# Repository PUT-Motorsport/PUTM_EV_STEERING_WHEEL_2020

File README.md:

# PUTM_EV_STEERING_WHEEL_2022

An overview of how I see this thing working:

* ~~Data gathered from IMU will be calculated into degrees and stored in buffers. These will be send out when the buffer is filled up.~~ 
* Interrupt will be triggered if a button is pressed. Then it will determine which button was pressed and send corresponding data. If, within specified, short time, there will occur another interrupt, then the programm will treat it as different action (two buttons pressed simultaneously). There will be 10 combinations: 4 single- and 6 simultaneous-presses.
* The scroll-like switches will trigger an interrupt if its position changes.

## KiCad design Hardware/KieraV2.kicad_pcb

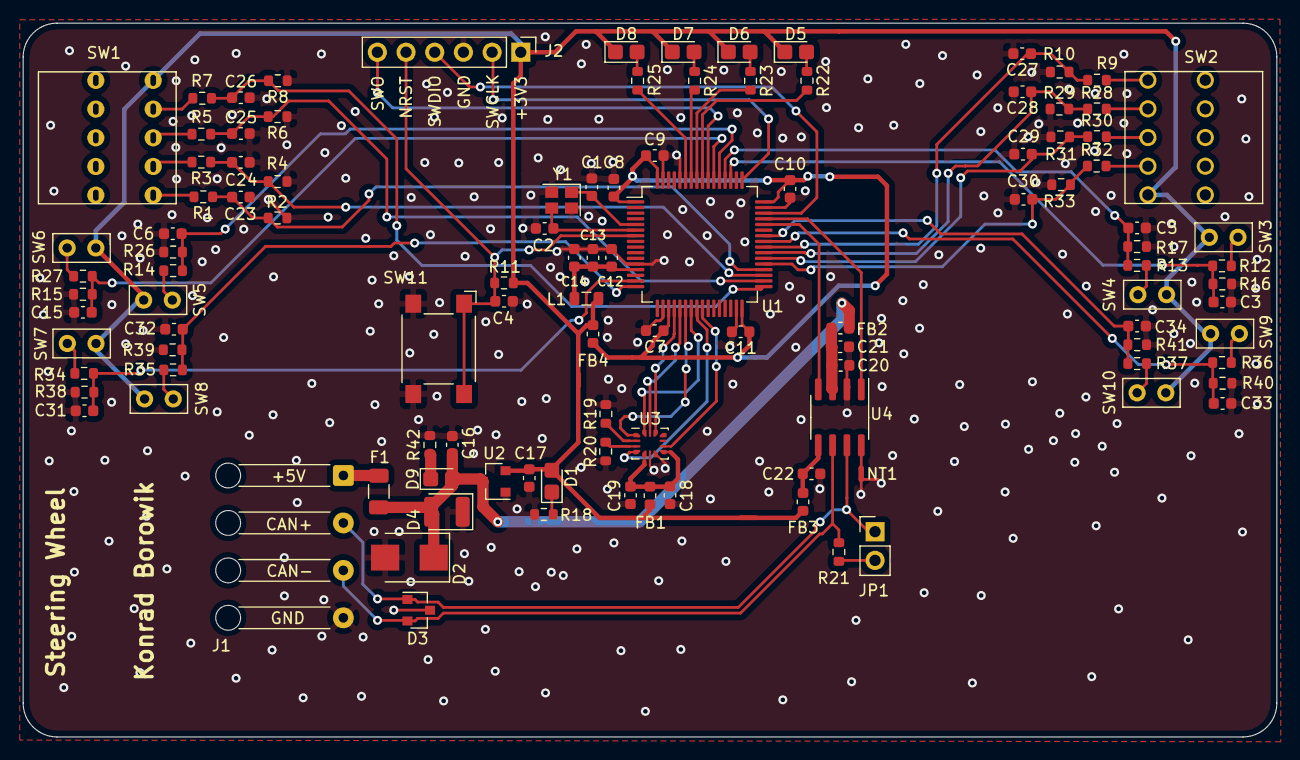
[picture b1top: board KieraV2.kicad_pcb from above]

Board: 2 copper layers, 111.0 x 63.2 mm, 111 parts (0 on the bottom side), 71 nets.

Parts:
C1, C2: 10pF; C_0603_1608Metric
C3, C4, C5, C6, C7, C8, C9, C12, C13, C15, C16, C17, C18, C19, C20, C22, C23, C24, C25, C26, C27, C28, C29, C30, C31, C32, C33, C34: 100nF; C_0603_1608Metric
C10, C11, C14, C21: 1uF; C_0603_1608Metric
D1, D5, D6, D7, D8, D9: LED; D_0805_2012Metric_Castellated
D2: D_Zener; D_SMB
D3: PESD2CAN.215; SOT-23
D4: D_TVS; D_1210_3225Metric
F1: Fuse_Small; Fuse_1206_3216Metric
FB1, FB2, FB3, FB4: 60R@100MHz; L_0603_1608Metric
J1: Conn_01x04_Male; SolderWire-0.25sqmm_1x04_P4.2mm_D0.65mm_OD1.7mm_Relief
J2: Conn_01x06_Male; PinHeader_1x06_P2.54mm_Vertical
JP1: CAN_termination_jumper; PinHeader_1x02_P2.54mm_Vertical
L1: L_Core_Ferrite_Small; L_0805_2012Metric
NT1: Net-Tie; NetTie-2_SMD_Pad0.5mm
R1, R3, R5, R7, R9, R12, R13, R14, R15, R18, R22, R23, R24, R25, R28, R30, R32, R34, R35, R36, R37, R42: 1k; R_0603_1608Metric
R2, R4, R6, R8, R10, R11, R16, R17, R26, R27, R29, R31, R33, R38, R39, R40, R41: 10k; R_0603_1608Metric
R19, R20: 0R; R_0603_1608Metric
R21: 120R; R_0603_1608Metric
SW1, SW2: SW_Rotary2x4
SW3, SW4, SW5, SW6, SW7, SW8, SW9, SW10: SW_Push; MyPushbuttonSwitch
SW11: SW_MEC_5G; SW_SPST_Omron_B3FS-100xP
U1: STM32L4P5RET6; LQFP-64_10x10mm_P0.5mm
U2: LM1117-3.3; SOT-23
U3: IMS330DHCX; LGA-14_3x2.5mm_P0.5mm_LayoutBorder3x4y
U4: ATA6561-GAQW-N; SOIC-8_3.9x4.9mm_P1.27mm
Y1: Crystal_GND24; Crystal_SMD_2520-4Pin_2.5x2.0mm

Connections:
+3V3: C17.1, D1.2, D5.1, D6.1, D7.1, D8.1, FB1.1, FB3.1, FB4.1, J2.1, L1.1, R11.1, SW1.1, SW2.1, SW3.1, SW4.1, SW5.1, SW6.1, SW7.1, SW8.1, SW9.1, SW10.1, U2.2
+5V: F1.1, J1.1
/+3V3_uC: C7.1, C8.1, C9.1, C10.1, C11.1, FB4.2, U1.1, U1.19, U1.32, U1.48, U1.64
/+3V3_uCa: C12.1, C13.1, C14.1, L1.2, U1.13
/CAN+: D3.1, J1.2, JP1.1, U4.7
/CAN-: D3.2, J1.3, R21.2, U4.6
/CAN/+3V3_VIO: C22.1, FB3.2, U4.5
/CAN/+5V_CAN_VDD: C20.1, C21.1, FB2.2, U4.3
/CAN/SHDN: NT1.1, U4.8
/CAN_RX: U1.44, U4.4
/CAN_TX: U1.45, U4.1
/ControlLED1: R22.2, U1.56
/ControlLED2: R23.2, U1.57
/ControlLED3: R24.2, U1.58
/ControlLED4: R25.2, U1.59
/IMU/+3.3V_IMU: C18.1, C19.1, FB1.2, U3.5, U3.8
/IMU/SCX: R20.2, U3.3
/IMU/SDX: R19.2, U3.2
/IMU_INT1: U1.24, U3.4
/IMU_INT2: U1.25, U3.9
/IMU_SPI1_CS: U1.20, U3.12
/IMU_SPI1_MISO: U1.22, U3.1
/IMU_SPI1_MOSI: U1.23, U3.14
/IMU_SPI1_SCK: U1.21, U3.13
/NRST: C4.1, J2.5, R11.2, SW11.1, SW11.2, U1.7
/OSC_IN: C1.1, U1.5, Y1.1
/OSC_OUT: C2.1, U1.6, Y1.3
/SW1_1: C26.1, R7.1, R8.2, U1.33
/SW1_2: C25.1, R5.1, R6.2, U1.34
/SW1_3: C24.1, R3.1, R4.2, U1.35
/SW1_4: C23.1, R1.1, R2.2, U1.36
/SW2_1: C30.1, R32.1, R33.2, U1.37
/SW2_2: C29.1, R30.1, R31.2, U1.38
/SW2_3: C28.1, R28.1, R29.2, U1.39
/SW2_4: C27.1, R9.1, R10.2, U1.40
/SW3: C3.1, R12.1, R16.2, U1.51
/SW4: C5.1, R13.1, R17.2, U1.52
/SW5: C6.1, R14.1, R26.2, U1.53
/SW6: C15.1, R15.1, R27.2, U1.54
/SW7: C31.1, R34.1, R38.2, U1.15
/SW8: C32.1, R35.1, R39.2, U1.16
/SW9: C33.1, R36.1, R40.2, U1.41
/SW10: C34.1, R37.1, R41.2, U1.42
/SWCLK: J2.2, U1.49
/SWDIO: J2.4, U1.46
/SWO: J2.6, U1.55
GND: C1.2, C2.2, C3.2, C4.2, C5.2, C6.2, C7.2, C8.2, C9.2, C10.2, C11.2, C12.2, C13.2, C14.2, C15.2, C16.2, C17.2, C18.2, C19.2, C20.2, C21.2, C22.2, C23.2, C24.2, C25.2, C26.2, C27.2, C28.2, C29.2, C30.2, C31.2, C32.2, C33.2, C34.2, D2.2, D3.3, D4.1, J1.4, J2.3, NT1.2, R2.1, R4.1, R6.1, R8.1, R10.1, R16.1, R17.1, R18.2, R19.1, R20.1, R26.1, R27.1, R29.1, R31.1, R33.1, R38.1, R39.1, R40.1, R41.1, R42.2, SW11.3, SW11.4, U1.12, U1.18, U1.31, U1.47, U1.60, U1.63, U2.1, U3.6, U3.7, U4.2, Y1.2, Y1.4
unnamed: D1.1, R18.1
unnamed: D5.2, R22.1
unnamed: D6.2, R23.1
unnamed: D7.2, R24.1
unnamed: D8.2, R25.1
unnamed: D9.1, R42.1
unnamed: JP1.2, R21.1
unnamed: R1.2, SW1.5
unnamed: R3.2, SW1.4
unnamed: R5.2, SW1.3
unnamed: R7.2, SW1.2
unnamed: R9.2, SW2.5
unnamed: R12.2, SW3.2
unnamed: R13.2, SW4.2
unnamed: R14.2, SW5.2
unnamed: R15.2, SW6.2
unnamed: R28.2, SW2.4
unnamed: R30.2, SW2.3
unnamed: R32.2, SW2.2
unnamed: R34.2, SW7.2
unnamed: R35.2, SW8.2
unnamed: R36.2, SW9.2
unnamed: R37.2, SW10.2
safe5V: C16.1, D2.1, D4.2, D9.2, F1.2, FB2.1, U2.3

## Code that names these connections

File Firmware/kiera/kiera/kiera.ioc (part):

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Mcu.Name=STM32L4P5R(G-E)Tx
Mcu.Package=LQFP64
Mcu.UserName=STM32L4P5RETx
PA1.GPIOParameters=GPIO_Label
PA1.GPIO_Label=SW7
PA1.Signal=GPIO_Input
PA11.Mode=CAN_Activate
PA11.Signal=CAN1_RX
PA12.Mode=CAN_Activate
PA12.Signal=CAN1_TX
PA13\ (JTMS/SWDIO).Mode=Serial_Wire
PA13\ (JTMS/SWDIO).Signal=SYS_JTMS-SWDIO
PA14\ (JTCK/SWCLK).Mode=Serial_Wire
PA14\ (JTCK/SWCLK).Signal=SYS_JTCK-SWCLK
PA2.GPIOParameters=GPIO_Label
PA2.GPIO_Label=SW8
PA2.Signal=GPIO_Input
PA4.Signal=SPI1_NSS
PA5.Signal=SPI1_SCK
PA6.Signal=SPI1_MISO
PA7.Signal=SPI1_MOSI
PA8.GPIOParameters=GPIO_Label
PA8.GPIO_Label=SW9
PA8.Signal=GPIO_Input
PA9.GPIOParameters=GPIO_Label
PA9.GPIO_Label=SW10
PA9.Signal=GPIO_Input
PB12.GPIOParameters=GPIO_Label
PB12.GPIO_Label=SW1_1
PB12.Signal=GPIO_Input
PB13.GPIOParameters=GPIO_Label
PB13.GPIO_Label=SW1_2
PB13.Signal=GPIO_Input
PB14.GPIOParameters=GPIO_Label
PB14.GPIO_Label=SW1_3
PB14.Signal=GPIO_Input
PB15.GPIOParameters=GPIO_Label
PB15.GPIO_Label=SW1_4
PB15.Signal=GPIO_Input
PB3\ (JTDO/TRACESWO).Signal=SYS_JTDO-SWO
PB4\ (NJTRST).GPIOParameters=GPIO_Label
PB4\ (NJTRST).GPIO_Label=ControlLed4
PB4\ (NJTRST).Signal=GPIO_Output
PB5.GPIOParameters=GPIO_Label
PB5.GPIO_Label=ControlLed3
PB5.Signal=GPIO_Output
PB6.GPIOParameters=GPIO_Label
PB6.GPIO_Label=ControlLed2
PB6.Signal=GPIO_Output
PB7.GPIOParameters=GPIO_Label
PB7.GPIO_Label=ControlLed1
PB7.Signal=GPIO_Output
PC10.GPIOParameters=GPIO_Label
PC10.GPIO_Label=SW3
PC10.Signal=GPIO_Input
PC11.GPIOParameters=GPIO_Label
PC11.GPIO_Label=SW4
PC11.Signal=GPIO_Input
PC12.GPIOParameters=GPIO_Label
PC12.GPIO_Label=SW5
PC12.Signal=GPIO_Input
PC4.GPIOParameters=GPIO_PuPd,GPIO_Label
PC4.GPIO_Label=IMU_INIT1
PC4.GPIO_PuPd=GPIO_PULLDOWN
PC4.Signal=GPXTI4
PC5.GPIOParameters=GPIO_PuPd,GPIO_Label
PC5.GPIO_Label=IMU_INIT2
PC5.GPIO_PuPd=GPIO_PULLDOWN
PC5.Signal=GPXTI5
PC6.GPIOParameters=GPIO_Label
PC6.GPIO_Label=SW2_1
PC6.Signal=GPIO_Input
PC7.GPIOParameters=GPIO_Label
PC7.GPIO_Label=SW2_2
PC7.Signal=GPIO_Input
PC8.GPIOParameters=GPIO_Label
PC8.GPIO_Label=SW2_3
PC8.Signal=GPIO_Input
PC9.GPIOParameters=GPIO_Label
PC9.GPIO_Label=SW2_4
PC9.Signal=GPIO_Input
PD2.GPIOParameters=GPIO_Label
PD2.GPIO_Label=SW6
PD2.Signal=GPIO_Input
PH0-OSC_IN\ (PH0).Mode=HSE-External-Oscillator
PH0-OSC_IN\ (PH0).Signal=RCC_OSC_IN
PH1-OSC_OUT\ (PH1).Mode=HSE-External-Oscillator
PH1-OSC_OUT\ (PH1).Signal=RCC_OSC_OUT
RCC.HSE_VALUE=8000000
RCC.SYSCLKFreq_VALUE=120000000
RCC.SYSCLKSource=RCC_SYSCLKSOURCE_PLLCLK
board=custom

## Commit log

2021-11-27 added .gitignore, SW_rotary_2x4
2021-11-27 added SWD pinout
2021-11-27 added VSS, connector for can and power
2021-11-27 power
2021-11-27 finished power scheme and some cosmetics
2021-11-27 uC supply added
2021-11-27 crystal part added
2021-11-27 added reset button
2021-11-27 ready to review
2021-11-28 removed resistor in crystal section
2021-11-28 10k resistor in reset
2021-11-28 cleanup
2021-11-30 changed resistor value in power scheme
2021-11-30 RC added by pushbuttons, changed capacitors in uC supply
2021-12-08 changed global labels to local, added IMU
2021-12-08 IMU.sch added
2021-12-08 added footprints, updated CAN, annotated symbols
2021-12-08 added temp pushbutton footprint
2021-12-08 small changes to footprints
2021-12-11 small changes to the electrical schematic, added footprints, first go at designing the pcb
2021-12-14 added button for starting procedure, changes to pcb layout pending
2021-12-15 controll leds are now groundend on uC, some changes of the pcb layout
2021-12-15 supplly lines are now thicc
2021-12-15 centering
2021-12-15 little more changes
2021-12-20 pcb layout
2021-12-21 redesigned layout
2021-12-21 power supply connector is now a micro-fit
2021-12-21 tiny adjustments
2021-12-28 rotary switches moved down
2021-12-28 IMU centered
2021-12-28 cutouts for quickrelease
2021-12-28 labels adjusted
2021-12-28 some more adjustments
2021-12-28 symbol changed, bigger cable hole in the middle
2021-12-28 bigger holes
2021-12-28 more adjustments
2022-01-06 redesigned PCB
2022-01-06 moved labels on pcb
2022-01-06 added logo
2022-01-06 added mounting holes
2022-01-07 moved mounting holes
2022-01-07 dimensions added
2022-01-07 hole adjustments
2022-01-11 new input 'connector', rearrangement
2022-01-11 added logos
2022-01-12 pcb changed
2022-01-12 new changes
2022-01-13 added gnd layers
2022-01-13 changed imu footprint
2022-01-13 aaaaa
2022-01-17 added 6pin connector and somme labels
2022-01-24 added ground
2022-01-24 filled properly
2022-01-24 more
2022-03-06 Program overview to discuss
2022-03-15 new flowchart
2022-04-02 fix - can rx&tx swapped
2022-04-02 fix - changed regulator model
2022-04-04 can on pcb updated
2022-05-10 wroking interrupts and dma
2022-05-12 simultaneous press works, but also detects single presses
2022-05-12 simultaneous press works and single presses too
2022-05-13 configuration for second adc, new variables for more buttons/scrolls
2022-05-13 code for 4 buttons
2022-05-13 functionality for every switch, passing adc readings to function doesn't work
2022-05-14 functions for scroll states work
2022-05-15 removed files
2022-05-15 include can library and cleanup
2022-05-22 sending frames
2022-05-23 buttons send frames
2022-05-26 gitignore
2022-05-28 can works
2022-06-01 removed resistor ladder
2022-06-01 rotary switches connected
2022-06-01 boot pin connected to gnd
2022-06-01 added more buttons
2022-06-01 refilled zones
2022-06-01 refilled gnd again
2022-06-02 changed positions for buttons
2022-06-06 Proposed fixes
2022-06-15 added fuse
2022-06-15 updated pcb
2022-06-21 temporary firmware
2022-06-21 compiled with 0 errors
2022-07-06 changed uC configuration
2022-07-06 sending frames from scrolls
2022-07-06 builds with errors
2022-07-07 project builds with updated code
2022-07-13 can setup
2022-07-18 annotating last frame
2022-07-19 working communication with dash, buttons are 1-4 from left to right
2022-07-19 before merge
2022-07-19 update 19/07/22
2023-04-04 firmware overhaul
2023-04-04 Revert "firmware overhaul"
    This reverts commit fc4f7325b2842b3143a277c0ec91c70f9f31444.
2023-07-01 sync local changes from some time ago with branch
2023-07-10 commented out heartbeat, cuz for some reason it makes the code enter error mode
